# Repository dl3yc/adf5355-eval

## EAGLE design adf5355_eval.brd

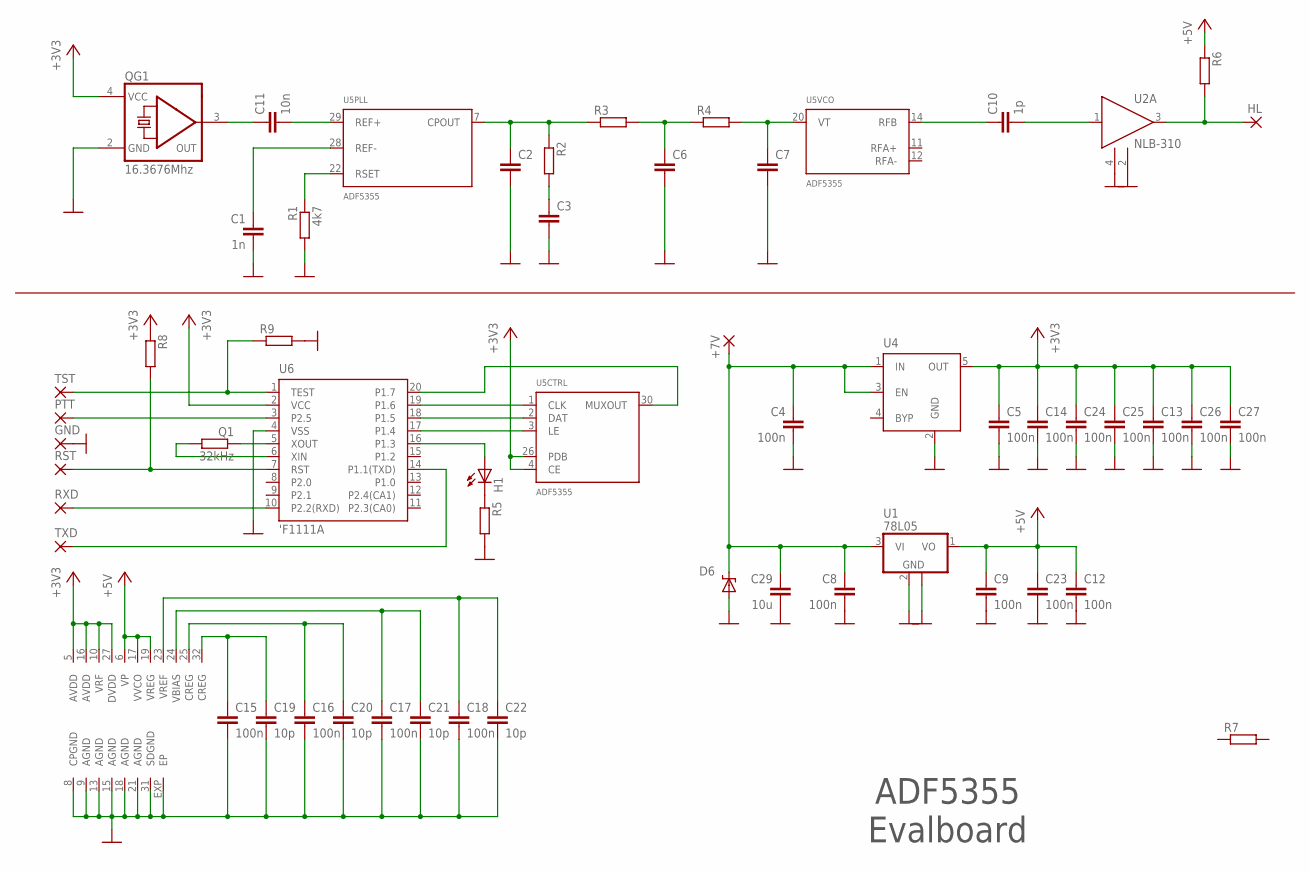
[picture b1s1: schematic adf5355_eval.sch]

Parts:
+7V: SMD2; SMD1,27-2,54
C1: 1n; C0402
C2, C3, C6, C7: C-EUC0402; C0402
C4, C8, C9, C14, C24: 100n; C0805
C5, C12, C13, C15, C16, C17, C18, C25, C26, C27: 100n; C0402
C10: 1p; C0603
C11: 10n; C0402
C19, C20, C21, C22: 10p; C0402
C23: 100n; C0603
C29: 10u; C0805
D6: SUPPRESSOR-SMBJ; SMBJ
GND: SMD2; SMD1,27-2,54
H1: PL006-WCR12; SOT23
HL: 1,6/0,9
PTT: SMD2; SMD1,27-2,54
Q1: 32kHz; R1206
QG1: 16.3676Mhz; CTS406
R1: 4k7; R0402
R2, R3, R4, R7, R8, R9: R-EU_R0402; R0402
R5, R6: R-EU_R0603; R0603
RST: SMD2; SMD1,27-2,54
RXD: SMD2; SMD1,27-2,54
TST: SMD2; SMD1,27-2,54
TXD: SMD2; SMD1,27-2,54
U1: 78L05; SOT89
U2: NLB-310; WW107
U4: MIC5219XX; SOT23-5
U5: ADF5355; LFCSP32
U6: 'F1111A; PW20

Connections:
+3V3: C5.1, C13.1, C14.1, C24.1, C25.1, C26.1, C27.1, QG1.4 (VCC), R8.1, U4.5 (OUT), U5.4 (CE), U5.5 (AVDD), U5.10 (VRF), U5.16 (AVDD), U5.26 (PDB), U5.27 (DVDD), U6.2 (VCC)
+5V: C9.1, C12.1, C23.1, R6.1, U1.1 (VO), U5.6 (VP), U5.17 (VVCO), U5.19 (VREG)
GND: C1.2, C2.2, C3.2, C4.2, C5.2, C6.2, C7.2, C8.2, C9.2, C12.2, C13.2, C14.2, C15.2, C16.2, C17.2, C18.2, C19.2, C20.2, C21.2, C22.2, C23.2, C24.2, C25.2, C26.2, C27.2, C29.2, D6.A, GND.1, QG1.2 (GND), R1.2, R5.2, R9.2, U1.2 (GND), U1.2@1 (GND), U2.2 (GND), U2.4 (GND), U4.2 (GND), U5.8 (CPGND), U5.9 (AGND), U5.13 (AGND), U5.15 (AGND), U5.18 (AGND), U5.21 (AGND), U5.31 (SDGND), U5.EXP (EP), U6.4 (VSS)
unnamed: C6.1, R3.2, R4.1
unnamed: C2.1, R2.1, R3.1, U5.7 (CPOUT)
unnamed: R1.1, U5.22 (RSET)
unnamed: C1.1, U5.28 (REF-)
unnamed: C7.1, R4.2, U5.20 (VT)
unnamed: +7V.1, C4.1, C8.1, C29.1, D6.C, U1.3 (VI), U4.1 (IN), U4.3 (EN)
unnamed: C11.2, U5.29 (REF+)
unnamed: C11.1, QG1.3 (OUT)
unnamed: C10.1, U5.14 (RFB)
unnamed: C10.2, U2.1 (IN)
unnamed: R9.1, TST.1, U6.1 (TEST)
unnamed: C3.1, R2.2
unnamed: HL.1, R6.2, U2.3 (OUT)
unnamed: R8.2, RST.1, U6.7 (RST)
unnamed: PTT.1, U6.3 (P2.5)
unnamed: H1.1 (A), U6.16 (P1.3)
unnamed: H1.3 (C), R5.1
unnamed: C18.1, C22.1, U5.23 (VREF)
unnamed: C17.1, C21.1, U5.24 (VBIAS)
unnamed: Q1.2, U6.6 (XIN)
unnamed: C16.1, C20.1, U5.25 (CREG)
unnamed: Q1.1, U6.5 (XOUT)
unnamed: C15.1, C19.1, U5.32 (CREG)
unnamed: RXD.1, U6.10 (P2.2(RXD))
unnamed: TXD.1, U6.14 (P1.1(TXD))
unnamed: U5.1 (CLK), U6.19 (P1.6)
unnamed: U5.2 (DAT), U6.18 (P1.5)
unnamed: U5.3 (LE), U6.17 (P1.4)
unnamed: U5.30 (MUXOUT), U6.20 (P1.7)

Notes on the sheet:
ADF5355 Evalboard

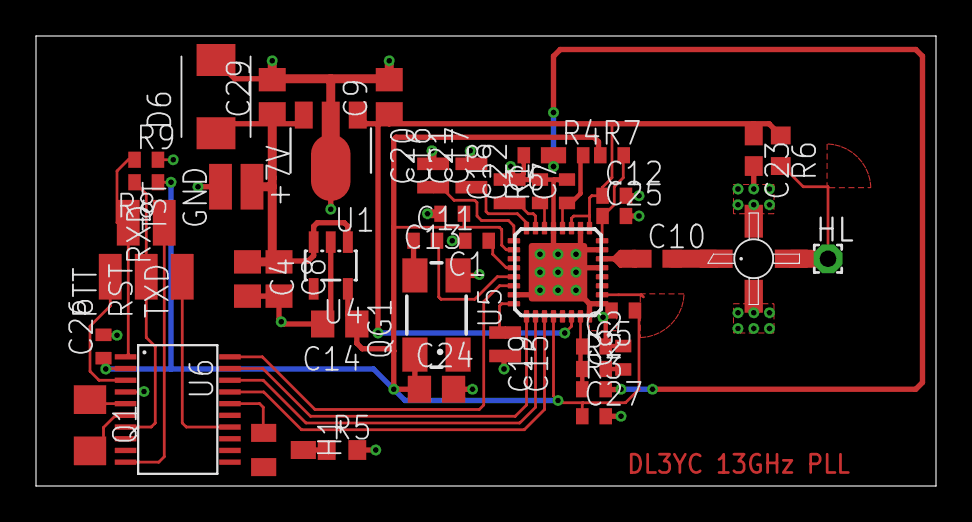
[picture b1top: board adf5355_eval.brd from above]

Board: 2 copper layers, 50.0 x 25.0 mm, 54 parts (0 on the bottom side), 32 nets.
